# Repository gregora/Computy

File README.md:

# Computy

An STM32 based flight computer

## Features

- **STM32F205 MCU**
- **BNO055 IMU** and **magnetometer**
- **GNSS** via UART
- **6 PWM** outputs for servos
- Receiver connection via UART
- Transparent serial telemetry radio via UART

## Hardware

Board specifictions:
- **50mm x 100mm** board size
- Four **M3** mounting holes
- **25Mhz** external oscilator

KiCAD files can be found in `/PCB` directory.

## Firmware

MCU is programmed with CubeIDE. Full project is located in `firmware/Computy`.

### Dependencies

- **[stm32-nmea-gps-hal](https://github.com/sztvka/stm32-nmea-gps-hal)** (**modified** and **included**)

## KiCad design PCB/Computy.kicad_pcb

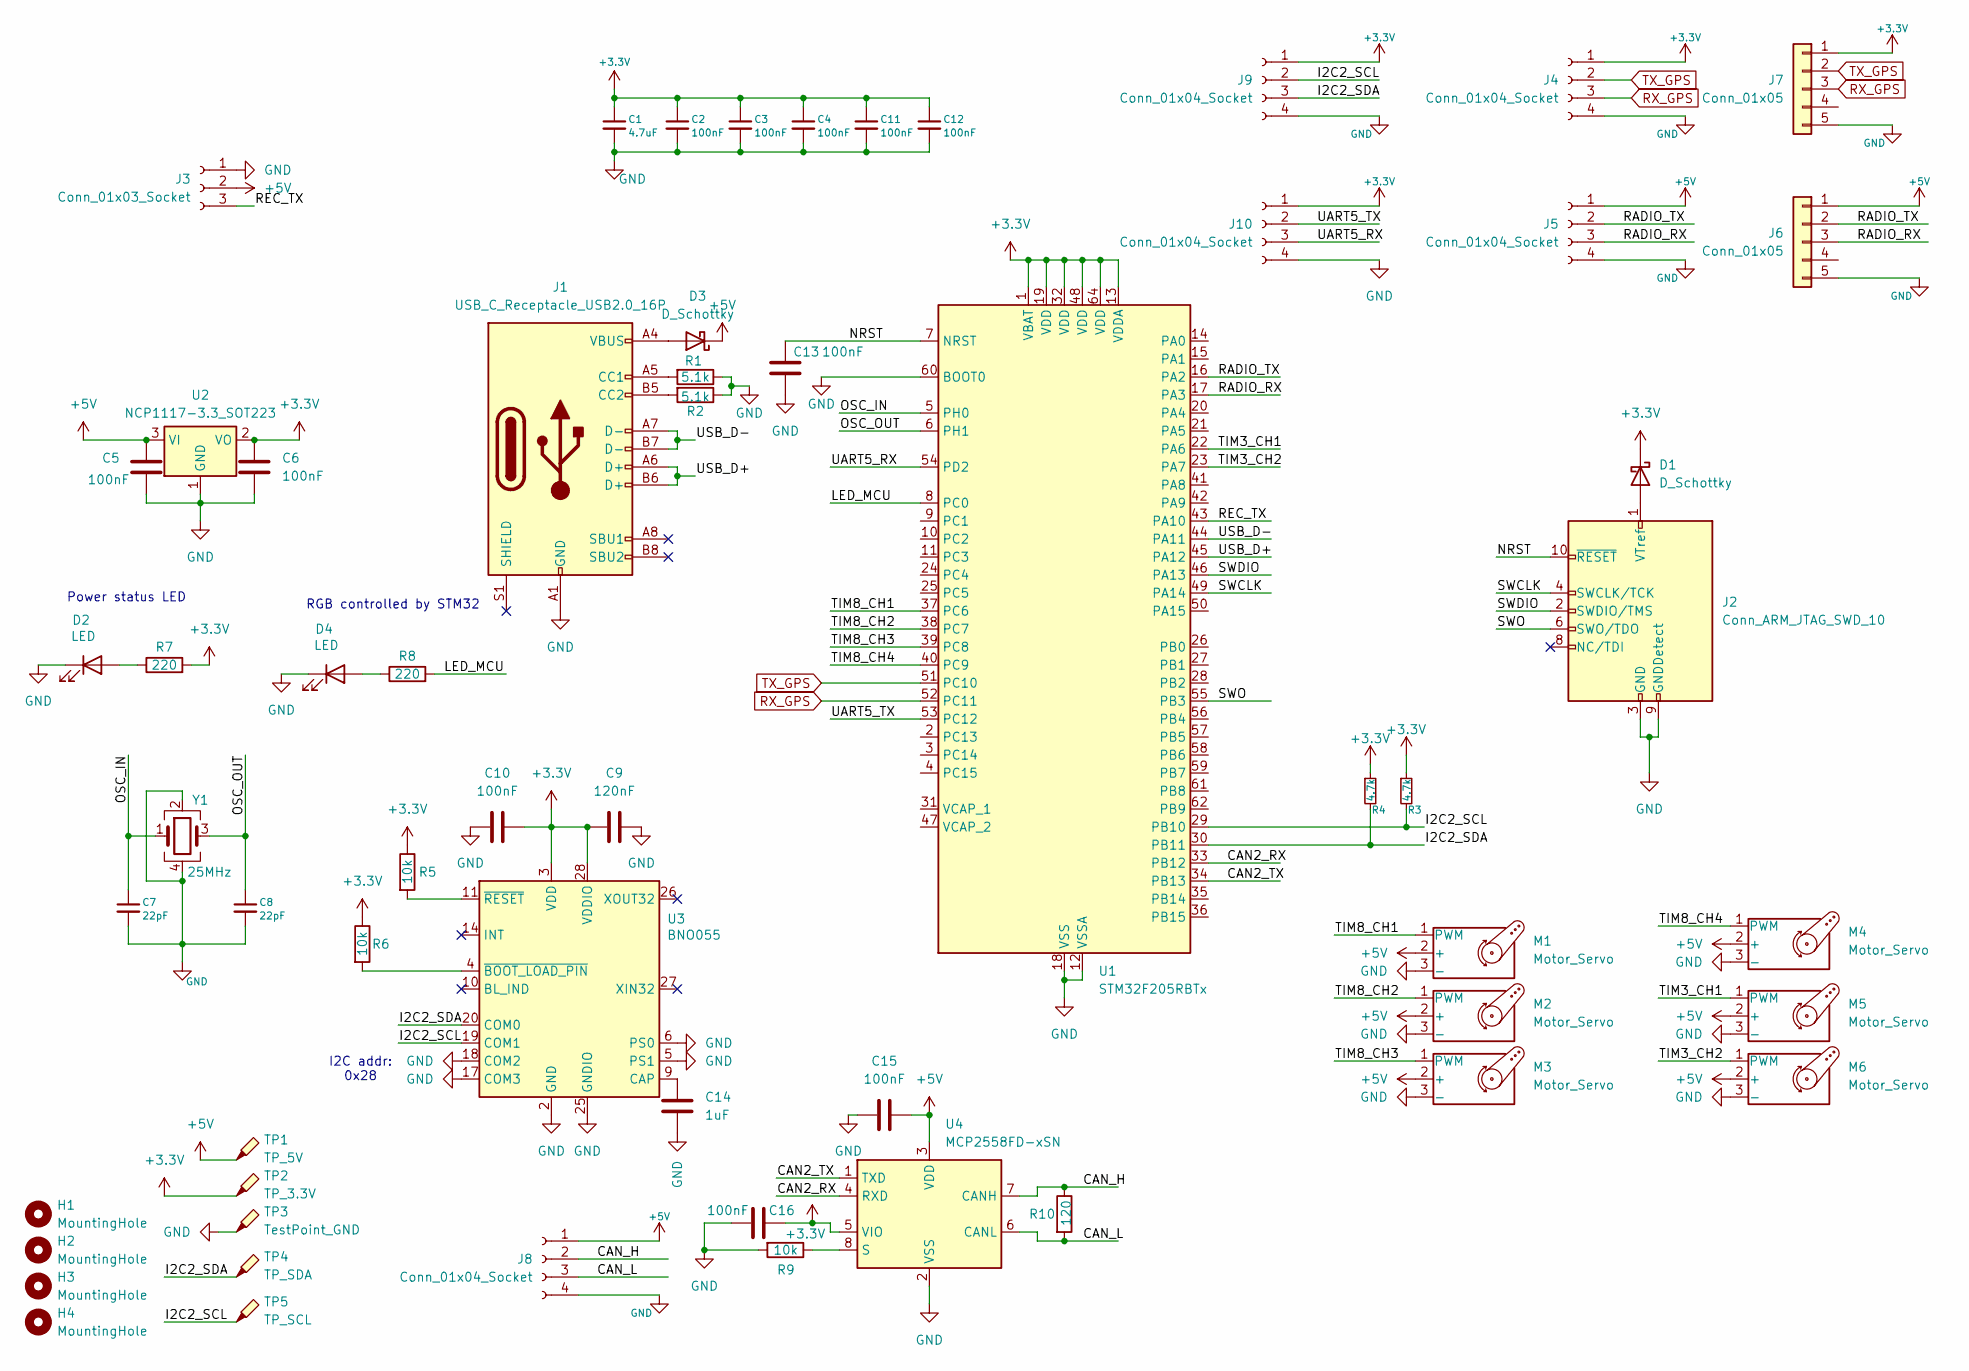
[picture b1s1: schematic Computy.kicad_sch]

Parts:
C1: 4.7uF; C_0805_2012Metric_Pad1.18x1.45mm_HandSolder
C2, C3, C4, C5, C6, C10, C11, C12, C13, C15, C16: 100nF; C_0805_2012Metric_Pad1.18x1.45mm_HandSolder
C7, C8: 22pF; C_0805_2012Metric_Pad1.18x1.45mm_HandSolder
C9: 120nF; C_0805_2012Metric_Pad1.18x1.45mm_HandSolder
C14: 1uF; C_0805_2012Metric_Pad1.18x1.45mm_HandSolder
D1, D3: D_Schottky; D_SOD-323_HandSoldering
D2, D4: LED; LED_0805_2012Metric_Pad1.15x1.40mm_HandSolder
H1, H2, H3, H4: MountingHole; MountingHole_3.2mm_M3_DIN965_Pad
J1: USB_C_Receptacle_USB2.0_16P; USB_C_Receptacle_GCT_USB4085
J2: Conn_ARM_JTAG_SWD_10; PinHeader_2x05_P2.54mm_Vertical
J3: Conn_01x03_Socket; PinSocket_1x03_P2.54mm_Vertical
J4, J5, J9, J10: Conn_01x04_Socket; PinSocket_1x04_P2.54mm_Vertical
J6, J7: Conn_01x05; Hirose_DF13-05P-1.25DSA_1x05_P1.25mm_Vertical
J8: Conn_01x04_Socket; PinHeader_1x04_P2.54mm_Vertical
M1, M2, M3, M4, M5, M6: Motor_Servo; PinHeader_1x03_P2.54mm_Vertical
R1, R2: 5.1k; R_0805_2012Metric_Pad1.20x1.40mm_HandSolder
R3, R4: 4.7k; R_0805_2012Metric_Pad1.20x1.40mm_HandSolder
R5, R6, R9: 10k; R_0805_2012Metric_Pad1.20x1.40mm_HandSolder
R7, R8: 220; R_0805_2012Metric_Pad1.20x1.40mm_HandSolder
R10: 120; R_0805_2012Metric_Pad1.20x1.40mm_HandSolder
TP1: TP_5V; TestPoint_THTPad_2.0x2.0mm_Drill1.0mm
TP2: TP_3.3V; TestPoint_THTPad_2.0x2.0mm_Drill1.0mm
TP3: TestPoint_GND; TestPoint_THTPad_2.0x2.0mm_Drill1.0mm
TP4: TP_SDA; TestPoint_THTPad_2.0x2.0mm_Drill1.0mm
TP5: TP_SCL; TestPoint_THTPad_2.0x2.0mm_Drill1.0mm
U1: STM32F205RBTx; LQFP-64_10x10mm_P0.5mm
U2: NCP1117-3.3_SOT223; SOT-223-3_TabPin2
U3: BNO055; LGA-28_5.2x3.8mm_P0.5mm
U4: MCP2558FD-xSN; SOIC-8_3.9x4.9mm_P1.27mm
Y1: 25MHz; Crystal_SMD_3225-4Pin_3.2x2.5mm_HandSoldering

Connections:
+3.3V: C1.1, C2.1, C3.1, C4.1, C6.1, C9.2, C10.2, C11.1, C12.1, C16.1, D1.1 (K), J4.1, J7.1, J9.1, J10.1, R3.1, R4.1, R5.1, R6.1, R7.2, TP2.1, U1.1 (VBAT), U1.13 (VDDA), U1.19 (VDD), U1.32 (VDD), U1.48 (VDD), U1.64 (VDD), U2.2 (VO), U3.3 (VDD), U3.28 (VDDIO), U4.5 (VIO)
+5V: C5.1, C15.1, D3.1 (K), J3.2, J5.1, J6.1, J8.1, M1.2 (+), M2.2 (+), M3.2 (+), M4.2 (+), M5.2 (+), M6.2 (+), TP1.1, U2.3 (VI), U4.3 (VDD)
/CAN2_RX: U1.33 (PB12), U4.4 (RXD)
/CAN2_TX: U1.34 (PB13), U4.1 (TXD)
/CAN_H: J8.2, R10.1, U4.7 (CANH)
/CAN_L: J8.3, R10.2, U4.6 (CANL)
/I2C2_SCL: J9.2, R3.2, TP5.1, U1.29 (PB10), U3.19 (COM1)
/I2C2_SDA: J9.3, R4.2, TP4.1, U1.30 (PB11), U3.20 (COM0)
/LED_MCU: R8.2, U1.8 (PC0)
/NRST: C13.1, J2.10 (~RESET), U1.7 (NRST)
/OSC_IN: C7.1, U1.5 (PH0), Y1.1
/OSC_OUT: C8.1, U1.6 (PH1), Y1.3
/RADIO_RX: J5.3, J6.3, U1.17 (PA3)
/RADIO_TX: J5.2, J6.2, U1.16 (PA2)
/REC_TX: J3.3, U1.43 (PA10)
/SWCLK: J2.4 (SWCLK/TCK), U1.49 (PA14)
/SWDIO: J2.2 (SWDIO/TMS), U1.46 (PA13)
/SWO: J2.6 (SWO/TDO), U1.55 (PB3)
/TIM3_CH1: M5.1 (PWM), U1.22 (PA6)
/TIM3_CH2: M6.1 (PWM), U1.23 (PA7)
/TIM8_CH1: M1.1 (PWM), U1.37 (PC6)
/TIM8_CH2: M2.1 (PWM), U1.38 (PC7)
/TIM8_CH3: M3.1 (PWM), U1.39 (PC8)
/TIM8_CH4: M4.1 (PWM), U1.40 (PC9)
/UART5_RX: J10.3, U1.54 (PD2)
/UART5_TX: J10.2, U1.53 (PC12)
/USB_D+: J1.A6 (D+), J1.B6 (D+), U1.45 (PA12)
/USB_D-: J1.A7 (D-), J1.B7 (D-), U1.44 (PA11)
GND: C1.2, C2.2, C3.2, C4.2, C5.2, C6.2, C7.2, C8.2, C9.1, C10.1, C11.2, C12.2, C13.2, C14.2, C15.2, C16.2, D2.1 (K), D4.1 (K), J1.A1 (GND), J1.A12 (GND), J1.B1 (GND), J1.B12 (GND), J2.3 (GND), J2.5 (GND), J2.9 (GNDDetect), J3.1, J4.4, J5.4, J6.5, J7.5, J8.4, J9.4, J10.4, M1.3 (-), M2.3 (-), M3.3 (-), M4.3 (-), M5.3 (-), M6.3 (-), R1.1, R2.1, R9.2, TP3.1, U1.12 (VSSA), U1.18 (VSS), U1.60 (BOOT0), U1.63 (VSS), U2.1 (GND), U3.2 (GND), U3.5 (PS1), U3.6 (PS0), U3.17 (COM3), U3.18 (COM2), U3.25 (GNDIO), U4.2 (VSS), Y1.2, Y1.4
unnamed: D1.2 (A), J2.1 (VTref)
unnamed: D2.2 (A), R7.1
unnamed: D3.2 (A), J1.A4 (VBUS), J1.A9 (VBUS), J1.B4 (VBUS), J1.B9 (VBUS)
unnamed: D4.2 (A), R8.1
unnamed: J1.A5 (CC1), R1.2
unnamed: J1.B5 (CC2), R2.2
unnamed: C14.1, U3.9 (CAP)
unnamed: R6.2, U3.4 (~BOOT_LOAD_PIN)
unnamed: R5.2, U3.11 (~RESET)
unnamed: R9.1, U4.8 (S)
RX_GPS: J4.3, J7.3, U1.52 (PC11)
TX_GPS: J4.2, J7.2, U1.51 (PC10)

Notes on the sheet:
I2C addr: 0x28
RGB controlled by STM32
Power status LED

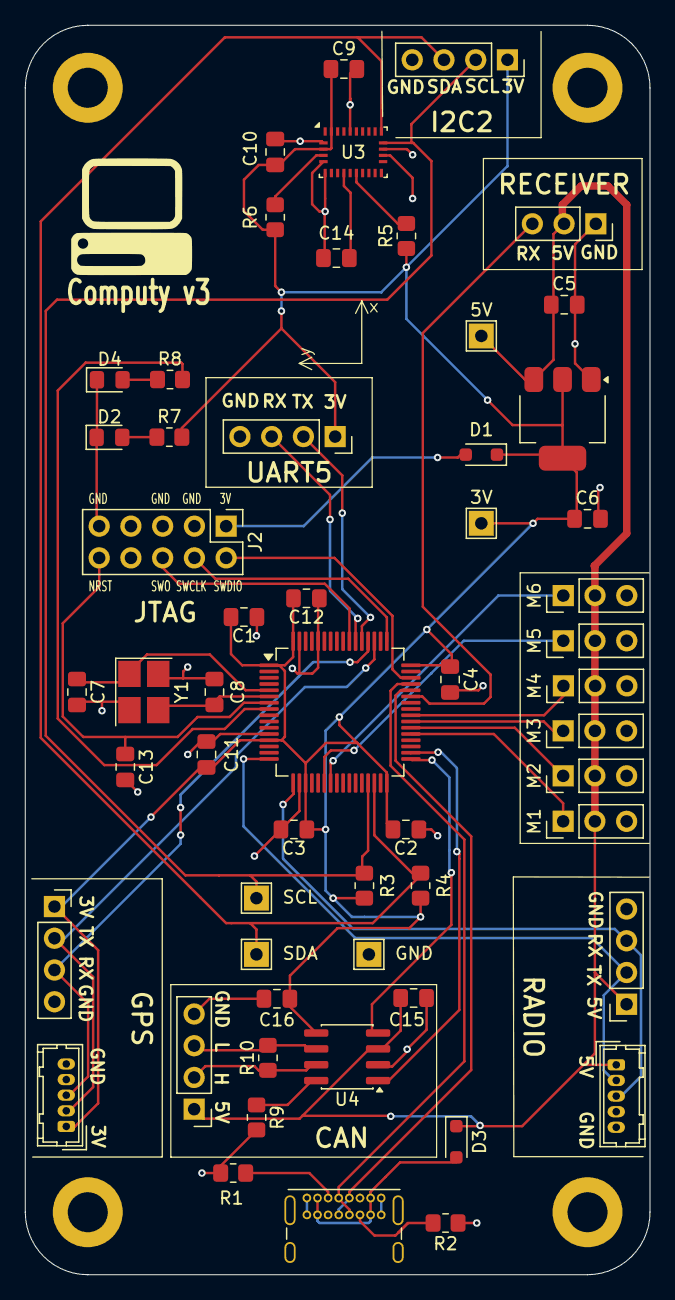
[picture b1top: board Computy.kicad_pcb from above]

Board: 2 copper layers, 50.0 x 100.0 mm, 60 parts (0 on the bottom side), 41 nets.

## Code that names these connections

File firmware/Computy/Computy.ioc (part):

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Mcu.Name=STM32F205R(B-C-E-F-G)Tx
Mcu.Package=LQFP64
Mcu.UserName=STM32F205RBTx
PA10.Mode=Asynchronous
PA10.Signal=USART1_RX
PA13.Mode=Trace_Asynchronous_SW
PA13.Signal=SYS_JTMS-SWDIO
PA14.Mode=Trace_Asynchronous_SW
PA14.Signal=SYS_JTCK-SWCLK
PA2.Mode=Asynchronous
PA2.Signal=USART2_TX
PA3.Mode=Asynchronous
PA3.Signal=USART2_RX
PA6.Signal=S_TIM3_CH1
PA7.Signal=S_TIM3_CH2
PA9.Mode=Asynchronous
PA9.Signal=USART1_TX
PB10.GPIOParameters=GPIO_Speed,GPIO_Pu
PB10.GPIO_Pu=GPIO_PULLUP
PB10.GPIO_Speed=GPIO_SPEED_FREQ_LOW
PB10.Mode=I2C
PB10.Signal=I2C2_SCL
PB11.GPIOParameters=GPIO_Speed,GPIO_Pu
PB11.GPIO_Pu=GPIO_PULLUP
PB11.GPIO_Speed=GPIO_SPEED_FREQ_MEDIUM
PB11.Mode=I2C
PB11.Signal=I2C2_SDA
PB12.Mode=CAN_Activate
PB12.Signal=CAN2_RX
PB13.Mode=CAN_Activate
PB13.Signal=CAN2_TX
PB3.Mode=Trace_Asynchronous_SW
PB3.Signal=SYS_JTDO-SWO
PB6.GPIOParameters=GPIO_PuPd
PB6.GPIO_PuPd=GPIO_PULLUP
PB6.Signal=GPIO_Output
PC0.Signal=GPIO_Output
PC10.Mode=Asynchronous
PC10.Signal=UART4_TX
PC11.Mode=Asynchronous
PC11.Signal=UART4_RX
PC12.Mode=Asynchronous
PC12.Signal=UART5_TX
PC6.Signal=S_TIM8_CH1
PC7.Signal=S_TIM8_CH2
PC8.Signal=S_TIM8_CH3
PC9.Signal=S_TIM8_CH4
PD2.Mode=Asynchronous
PD2.Signal=UART5_RX
PH0-OSC_IN.Mode=HSE-External-Oscillator
PH0-OSC_IN.Signal=RCC_OSC_IN
PH1-OSC_OUT.Mode=HSE-External-Oscillator
PH1-OSC_OUT.Signal=RCC_OSC_OUT
RCC.HSE_VALUE=25000000
RCC.SYSCLKFreq_VALUE=16000000
board=custom

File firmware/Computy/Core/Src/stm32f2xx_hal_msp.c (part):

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
    __HAL_RCC_GPIOB_CLK_ENABLE();
    /**CAN2 GPIO Configuration
    PB12     ------> CAN2_RX
    PB13     ------> CAN2_TX
    */
    GPIO_InitStruct.Pin = GPIO_PIN_12|GPIO_PIN_13;
    GPIO_InitStruct.Mode = GPIO_MODE_AF_PP;
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    __HAL_RCC_CAN1_CLK_DISABLE();

    /**CAN2 GPIO Configuration
    PB12     ------> CAN2_RX
    PB13     ------> CAN2_TX
    */
    HAL_GPIO_DeInit(GPIOB, GPIO_PIN_12|GPIO_PIN_13);

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
    __HAL_RCC_GPIOB_CLK_ENABLE();
    /**I2C2 GPIO Configuration
    PB10     ------> I2C2_SCL
    PB11     ------> I2C2_SDA
    */
    GPIO_InitStruct.Pin = GPIO_PIN_10;
    GPIO_InitStruct.Mode = GPIO_MODE_AF_OD;
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    __HAL_RCC_I2C2_CLK_DISABLE();

    /**I2C2 GPIO Configuration
    PB10     ------> I2C2_SCL
    PB11     ------> I2C2_SDA
    */
    HAL_GPIO_DeInit(GPIOB, GPIO_PIN_10);

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
    __HAL_RCC_GPIOC_CLK_ENABLE();
    /**TIM8 GPIO Configuration
    PC6     ------> TIM8_CH1
    */
    GPIO_InitStruct.Pin = GPIO_PIN_6;
    GPIO_InitStruct.Mode = GPIO_MODE_AF_PP;
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    /* USER CODE END TIM3_MspPostInit 0 */
    __HAL_RCC_GPIOA_CLK_ENABLE();
    /**TIM3 GPIO Configuration
    PA6     ------> TIM3_CH1
    PA7     ------> TIM3_CH2
    */
    GPIO_InitStruct.Pin = GPIO_PIN_6|GPIO_PIN_7;
    GPIO_InitStruct.Mode = GPIO_MODE_AF_PP;
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
    __HAL_RCC_GPIOC_CLK_ENABLE();
    /**TIM8 GPIO Configuration
    PC7     ------> TIM8_CH2
    PC8     ------> TIM8_CH3
    PC9     ------> TIM8_CH4
    */
    GPIO_InitStruct.Pin = GPIO_PIN_7|GPIO_PIN_8|GPIO_PIN_9;
    GPIO_InitStruct.Mode = GPIO_MODE_AF_PP;
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    __HAL_RCC_TIM8_CLK_DISABLE();

    /**TIM8 GPIO Configuration
    PC6     ------> TIM8_CH1
    PC7     ------> TIM8_CH2
    PC8     ------> TIM8_CH3
    PC9     ------> TIM8_CH4
    */
    HAL_GPIO_DeInit(GPIOC, GPIO_PIN_6|GPIO_PIN_7|GPIO_PIN_8|GPIO_PIN_9);

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
    __HAL_RCC_GPIOC_CLK_ENABLE();
    /**UART4 GPIO Configuration
    PC10     ------> UART4_TX
    PC11     ------> UART4_RX
    */
    GPIO_InitStruct.Pin = GPIO_PIN_10|GPIO_PIN_11;
    GPIO_InitStruct.Mode = GPIO_MODE_AF_PP;
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    __HAL_RCC_GPIOC_CLK_ENABLE();
    __HAL_RCC_GPIOD_CLK_ENABLE();
    /**UART5 GPIO Configuration
    PC12     ------> UART5_TX
    PD2     ------> UART5_RX
    */
    GPIO_InitStruct.Pin = GPIO_PIN_12;
    GPIO_InitStruct.Mode = GPIO_MODE_AF_PP;
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    __HAL_RCC_GPIOA_CLK_ENABLE();
    /**USART1 GPIO Configuration
    PA9     ------> USART1_TX
    PA10     ------> USART1_RX
    */
    GPIO_InitStruct.Pin = GPIO_PIN_9|GPIO_PIN_10;
    GPIO_InitStruct.Mode = GPIO_MODE_AF_PP;
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
    __HAL_RCC_GPIOA_CLK_ENABLE();
    /**USART2 GPIO Configuration
    PA2     ------> USART2_TX
    PA3     ------> USART2_RX
    */
    GPIO_InitStruct.Pin = GPIO_PIN_2|GPIO_PIN_3;
    GPIO_InitStruct.Mode = GPIO_MODE_AF_PP;
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    __HAL_RCC_UART4_CLK_DISABLE();

    /**UART4 GPIO Configuration
    PC10     ------> UART4_TX
    PC11     ------> UART4_RX
    */
    HAL_GPIO_DeInit(GPIOC, GPIO_PIN_10|GPIO_PIN_11);

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    __HAL_RCC_UART5_CLK_DISABLE();

    /**UART5 GPIO Configuration
    PC12     ------> UART5_TX
    PD2     ------> UART5_RX
    */
    HAL_GPIO_DeInit(GPIOC, GPIO_PIN_12);

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
    /**USART1 GPIO Configuration
    PA9     ------> USART1_TX
    PA10     ------> USART1_RX
    */
    HAL_GPIO_DeInit(GPIOA, GPIO_PIN_9|GPIO_PIN_10);

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    __HAL_RCC_USART2_CLK_DISABLE();

    /**USART2 GPIO Configuration
    PA2     ------> USART2_TX
    PA3     ------> USART2_RX
    */
    HAL_GPIO_DeInit(GPIOA, GPIO_PIN_2|GPIO_PIN_3);

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
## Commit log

2025-05-21 Add firmware
2025-05-21 Remove unnecessary file
2025-05-21 Minor changes to firmware
2025-05-21 Update .gitignore and minor changes to the PCB
2025-05-22 Update launch file for updated firmware
2025-05-27 Add a picture
2025-05-27 Computy v2
    - Fix issues with the PCB
    - Connect SWO
    - Connect CC1101 to SPI1
    - Fix BNO055 SCL and SDA
    - Add more testpoints
    - Update firmware
2025-05-27 Update media
2025-05-27 Minor changes to PCB
2025-05-27 Minor PCB changes
2025-05-29 Improve GPS connectivity
2025-05-29 Set up TIM2 for performance measurements
2025-05-29 Measure fixes per second for the GPS
2025-06-14 Update firmware for Computy v2
2025-06-15 Move to internal clock
2025-06-15 Add the library for reading data from IMU
2025-06-15 Minor refactoring in main.c
2025-06-15 Read angular velocity
2025-06-15 Correct comment in bno055
2025-06-15 Major fix - Set I2C2 to high speed mode which seems to fix HAL_BUSY error
2025-06-15 Change duty cycle for i2c2
2025-06-19 Add CC1101 drivers
2025-07-05 Add cc1101 code - written by me
2025-07-06 First working version with cc1101 module
2025-07-06 Implement data sending over te radio
2025-07-06 Add axis remap option and quaternion operations
2025-07-30 Update IMU reading with 'software' axis remapping
2025-07-30 MAJOR: Final fix for axis remapping
2025-07-31 iBus to PWM bug fix
2025-07-31 Fix I2C on startup bug - Add delay of 500ms
2025-08-01 Somewhat improve radio link range
2025-08-17 Correctly implement checksum for ibus
2025-08-17 Only accept ibus messages with the correct checksum
2025-08-17 Bug fix
2025-08-17 Add firmware specifications
2025-08-17 Add mode determination and first control logic
2025-08-17 Add D component to PID for Mode 1
2025-08-17 Fix mistake in firmware specifications
2025-08-20 Activate take-off mode with channel 6
2025-08-21 Retune control system
2025-08-22 Add DMA ibus reading
2025-08-22 Remove unnecessary comments
2025-08-22 Improve GPS parsing
2025-08-22 Other minor changes
2025-08-24 Move parse_ibus to a seperate file
2025-08-24 Remove unnecessary DMA calls
2025-09-13 Add quaternion conjugation and quaternion vector transformation to quaternion.h
2025-09-13 Fix transformation to NED (north-east-down)
2025-09-13 Update readme with the new specifications
2025-09-13 Add Automatic mode
2025-09-13 Add P controller for bearing
2025-09-13 Update P values for bearing
2025-09-13 Return P value to original
2025-09-13 Minor changes
2025-09-13 Add dt
2025-09-15 Update PID values
2025-09-18 Add coordinates.h, a file for storing private gps coordinates
2025-09-18 Add coordinates.h to gitignore
2025-09-18 Untrack coordinates.h
2025-09-18 Add CMSIS-DSP library
2025-09-18 Add kalman.h to project
2025-09-18 Correctly add CMSIS-DSP library
2025-09-19 Readd kalman.h and kalman.c
2025-09-20 First working version with Kalman filter
2025-09-20 Correct acceleration local to global transformation
2025-10-01 [UNTESTED] Increase pitch gains and add bank angle compensation
2025-10-03 Enable waypoint missions
2025-10-04 Improve trim values, emergency conditions and parameters
2025-10-07 Update P value for heading
2025-10-08 Add 3DR transparent radio support
2025-10-08 Add ground station software for 3dr radio
2025-10-09 Correct comments
2025-10-09 Add rotating bug when drawing position
2025-10-09 Move ground serial data reading to a separate thread
2025-10-09 Minor readme update
2025-10-10 Ground control bug fixes
2025-10-10 Update timeouts and ground station
2025-10-10 Transmit data in a single call
2025-10-11 Bug fixes on ground station
2025-10-17 Ground station bug fixes
2025-10-17 Bug fixes
2025-10-18 Add connect and disconnect sound effects to ground station
2025-10-18 NMEA parse memory leak fix
2025-10-18 Improve analysis tool and decrease telemetry period to 15ms
2025-10-18 Optionally visualize key points in analyze.py
2025-10-19 Add update rate for gps
2025-10-19 Set GPS frequency to 2Hz
2025-10-19 Add port scanning
2025-10-19 Simplify minimap rendering
2025-10-19 Add angular velocities to the packet instead of accelerations
2025-12-07 Add DF13 connector for GPS and telemetry
2025-12-07 Add LED to board
2025-12-07 Add CAN transceiver
2025-12-08 PCB fixes
2025-12-08 Minor layout changes
2025-12-08 Expose UART5 and I2C2 on the PCB
2026-02-24 Add blinking LED and correct a couple other small things
2026-02-24 Bug fix on radio UART
2026-02-26 Add parameter receiving via radio
2026-02-26 Package parameter sending into a function
2026-02-27 Add parameter checksum and parameter editing
2026-02-27 Add config files for parameters
2026-02-28 Add parameter loading on GUI startup
2026-02-28 Add servo trims as parameters
2026-02-28 Add time between telemetry transmissions as parameter
2026-02-28 Add waypoint loading to ground station
2026-02-28 Add default mission
2026-02-28 Add mission registers to flight computer
2026-02-28 Dynamically change the mission profile
2026-02-28 Add file names to ground UI
2026-02-28 Ground UI improvement
2026-02-28 Add completion radius as parameter
2026-02-28 Fix UART1 DMA mistake
2026-03-19 Fix the bug with DMA on UART1 randomly stopping (restart it on error)

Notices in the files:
firmware/Computy/Core/Src/stm32f2xx_hal_msp.c:
Copyright (c) 2025 STMicroelectronics.
All rights reserved.
This software is licensed under terms that can be found in the LICENSE file
